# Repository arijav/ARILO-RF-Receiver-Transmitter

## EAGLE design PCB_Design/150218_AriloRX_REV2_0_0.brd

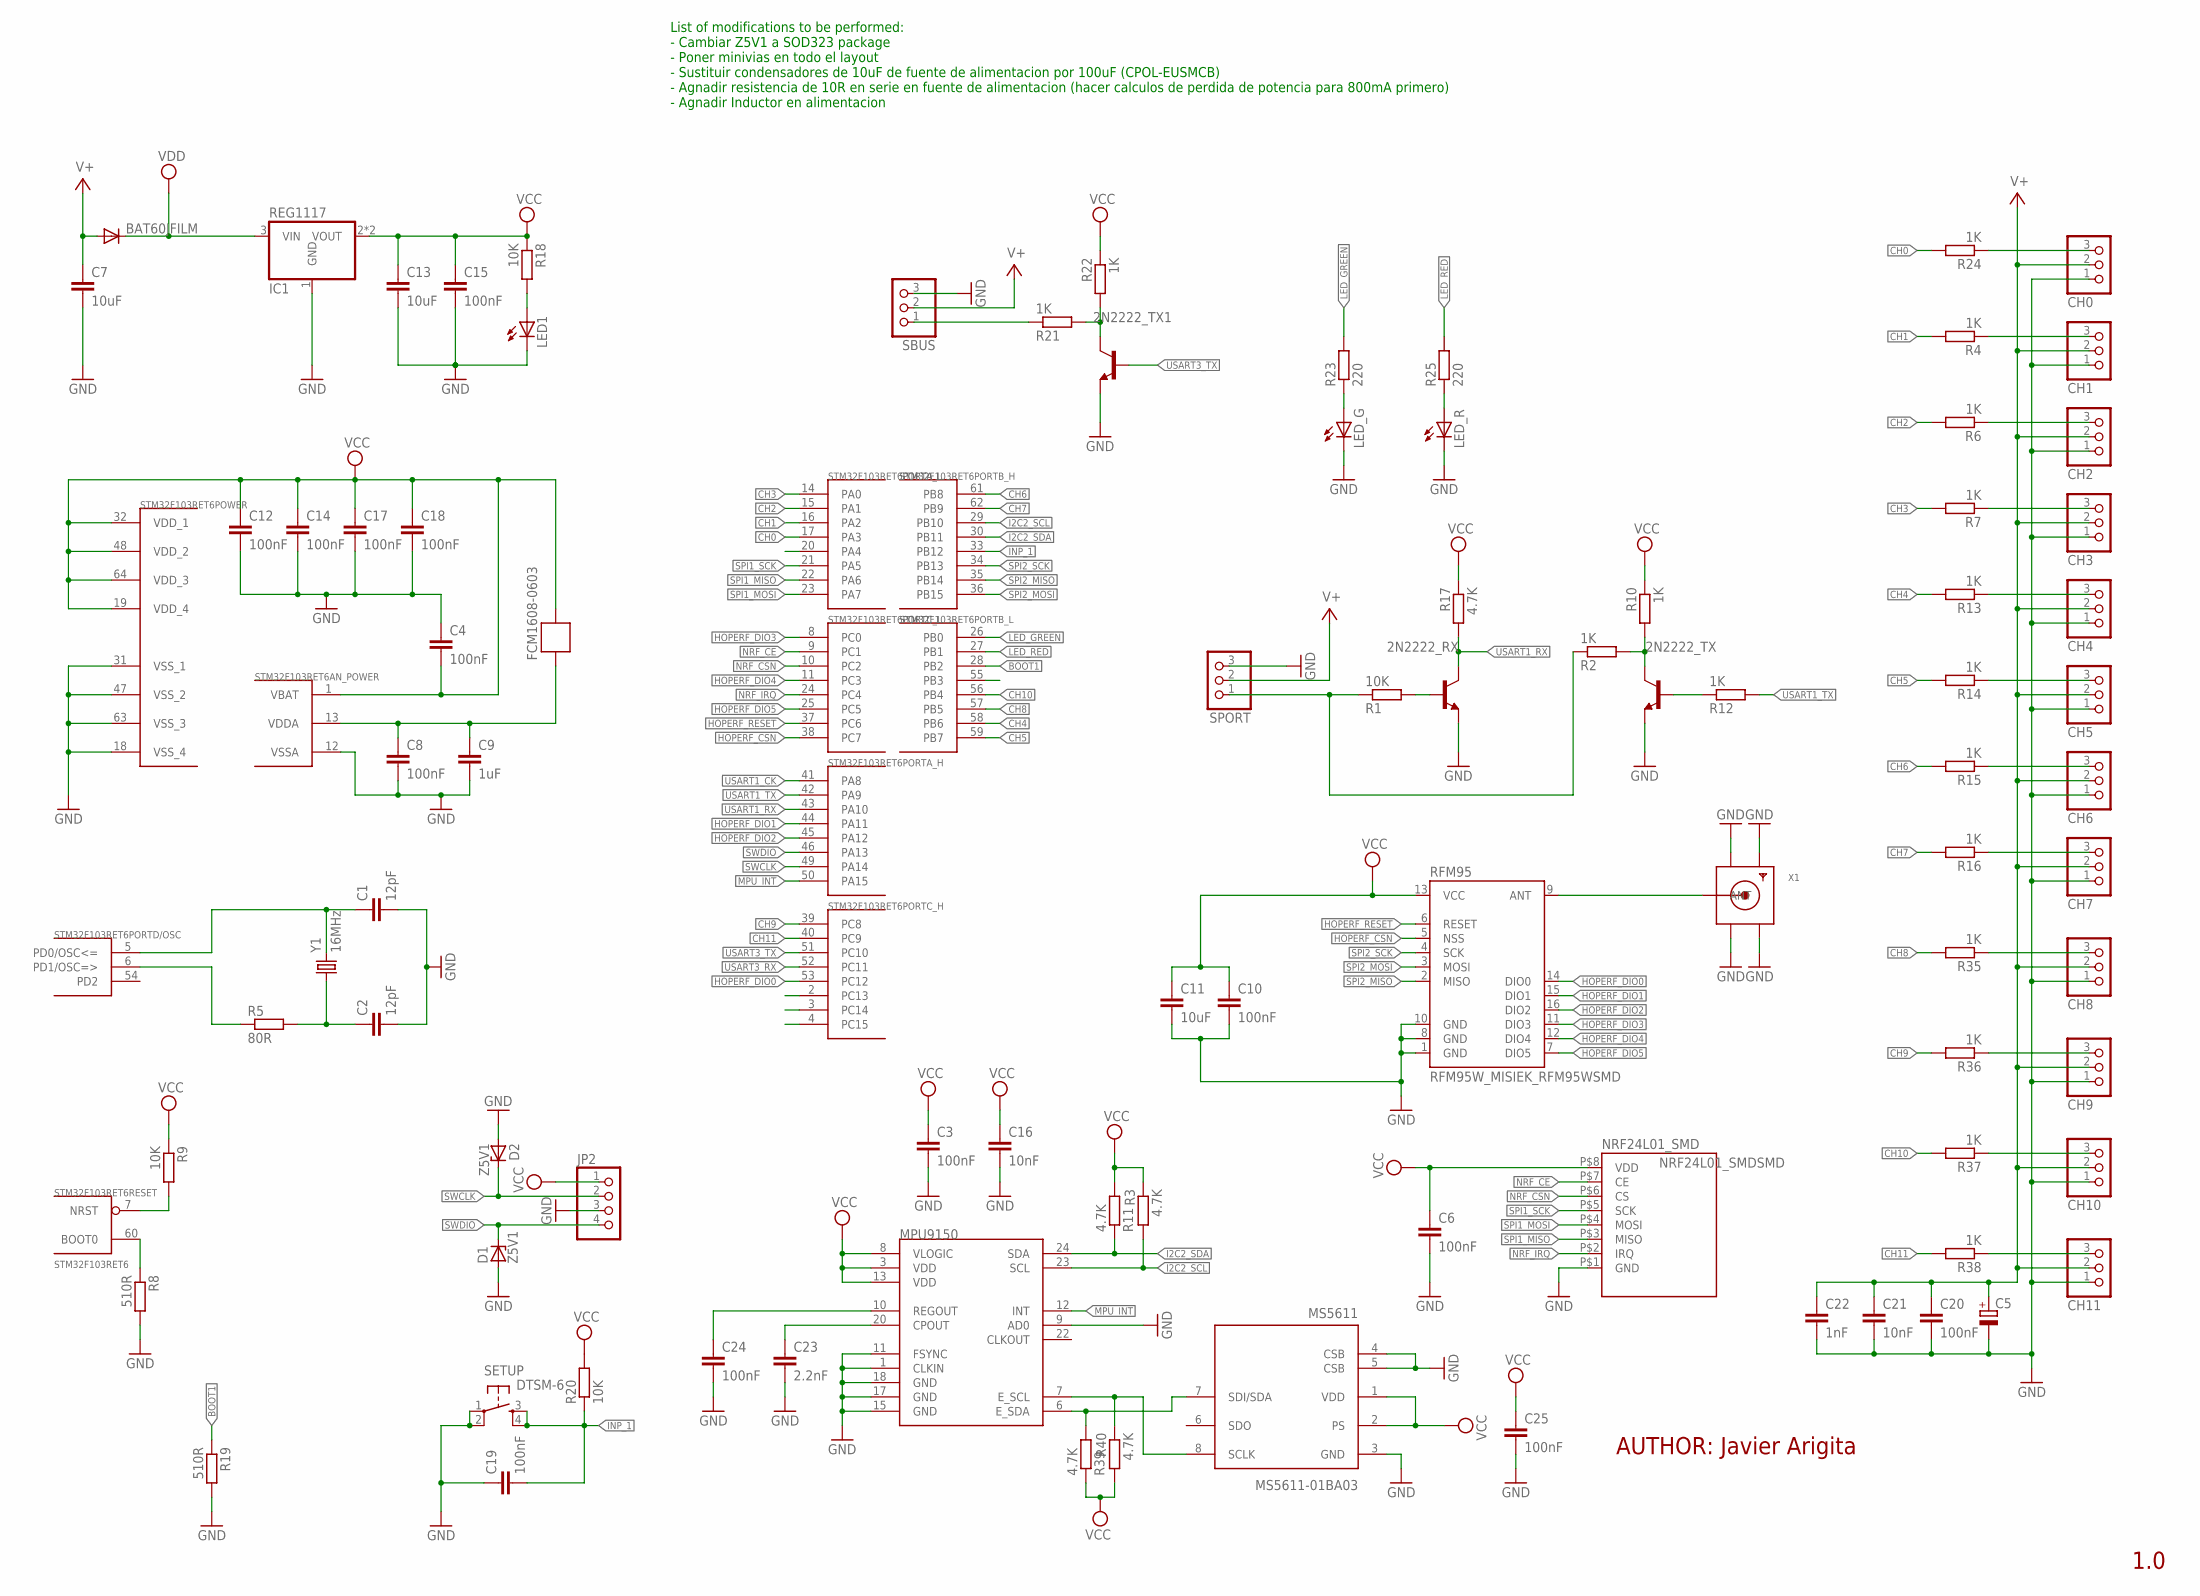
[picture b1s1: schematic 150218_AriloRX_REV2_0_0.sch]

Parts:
2N2222_RX, 2N2222_TX, 2N2222_TX1: MMBT2222ALT1-NPN-SOT23-BEC; SOT23-BEC
BAT60JFILM: DIODE-SOD323-R; SOD323-R
C1, C2: 12pF; RESISTOR_C0603
C3, C4, C6, C8, C10, C12, C14, C15, C17, C18, C19, C20, C24, C25: 100nF; RESISTOR_C0603
C5: CPOL-EUSMCB; SMC_B
C7, C11, C13: 10uF; RESISTOR_C3216
C9: 1uF; RESISTOR_C0603
C16, C21: 10nF; RESISTOR_C0603
C22: 1nF; RESISTOR_C0603
C23: 2.2nF; RESISTOR_C0603
CH0, CH1, CH2, CH3, CH4, CH5, CH6, CH7, CH8, CH9, CH10, CH11: PINHD-1X3; 1X03
D1, D2: Z5V1; SOD80C
FCM1608-0603: FERRITE-BEAD; R0603
IC1: REG1117; SOT223
JP2: PINHD-1X4; 1X04
LED1: LED_LEDCHIP-LED0603; LED_CHIP-LED0603
LED_G: LEDCHIP-LED0603; CHIP-LED0603
LED_R: LEDCHIP-LED0603; CHIP-LED0603
MPU9150: MPU-9150QFN-24-NP; QFN-24-NP
MS5611: MS5611-01BA03; SON125P300X500X100-8N
NRF24L01_SMD: NRF24L01_SMDSMD; NRF24L01_SMD
R1, R9, R18, R20: 10K; RCL_R0603
R2, R4, R6, R7, R10, R12, R13, R14, R15, R16, R21, R22, R24, R35, R36, R37, R38: 1K; RCL_R0603
R3, R11, R17, R39, R40: 4.7K; RCL_R0603
R5: 80R; RCL_R0603
R8, R19: 510R; RCL_R0603
R23, R25: 220; RCL_R0603
RFM95: RFM95W_MISIEK_RFM95WSMD; RFM95W_MISIEK_RFM95W_SMD
SBUS: PINHD-1X3; 1X03
SETUP: DTSM-6
SPORT: PINHD-1X3; 1X03
STM32F103RET6: STM32F103RET6; TQFP64
X1: SMACONNECTOR_EDGE; SMA_EDGELAUNCH
Y1: 16MHz; CRYSTAL-SMD-5X3

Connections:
BOOT1: R19.1, STM32F103RET6.28 (PB2)
CH0: R24.2, STM32F103RET6.17 (PA3)
CH1: R4.2, STM32F103RET6.16 (PA2)
CH2: R6.2, STM32F103RET6.15 (PA1)
CH3: R7.2, STM32F103RET6.14 (PA0)
CH4: R13.2, STM32F103RET6.58 (PB6)
CH5: R14.2, STM32F103RET6.59 (PB7)
CH6: R15.2, STM32F103RET6.61 (PB8)
CH7: R16.2, STM32F103RET6.62 (PB9)
CH8: R35.2, STM32F103RET6.57 (PB5)
CH9: R36.2, STM32F103RET6.39 (PC8)
CH10: R37.2, STM32F103RET6.56 (PB4)
CH11: R38.2, STM32F103RET6.40 (PC9)
GND: 2N2222_RX.E, 2N2222_TX.E, 2N2222_TX1.E, C1.2, C2.2, C3.2, C4.1, C5.-, C6.2, C7.2, C8.2, C9.2, C10.2, C11.2, C12.2, C13.2, C14.2, C15.2, C16.2, C17.2, C18.2, C19.1, C20.2, C21.2, C22.2, C23.2, C24.2, C25.2, CH0.1, CH1.1, CH2.1, CH3.1, CH4.1, CH5.1, CH6.1, CH7.1, CH8.1, CH9.1, CH10.1, CH11.1, D1.A, D2.A, IC1.1 (GND), JP2.3, LED1.C, LED_G.C, LED_R.C, MPU9150.1 (CLKIN), MPU9150.9 (AD0), MPU9150.11 (FSYNC), MPU9150.15 (GND), MPU9150.17 (GND), MPU9150.18 (GND), MS5611.3 (GND), MS5611.4 (CSB), MS5611.5 (CSB), NRF24L01_SMD.P$1 (GND), R8.2, R19.2, RFM95.1 (GND), RFM95.8 (GND), RFM95.10 (GND), SBUS.3, SETUP.1, SETUP.2, SPORT.3, STM32F103RET6.12 (VSSA), STM32F103RET6.18 (VSS_4), STM32F103RET6.31 (VSS_1), STM32F103RET6.47 (VSS_2), STM32F103RET6.63 (VSS_3), X1.GND@1 (GND4), X1.GND@2 (GND3), X1.GND@3 (GND2), X1.GND@4 (GND1)
HOPERF_CSN: RFM95.5 (NSS), STM32F103RET6.38 (PC7)
HOPERF_DIO0: RFM95.14 (DIO0), STM32F103RET6.53 (PC12)
HOPERF_DIO1: RFM95.15 (DIO1), STM32F103RET6.44 (PA11)
HOPERF_DIO2: RFM95.16 (DIO2), STM32F103RET6.45 (PA12)
HOPERF_DIO3: RFM95.11 (DIO3), STM32F103RET6.8 (PC0)
HOPERF_DIO4: RFM95.12 (DIO4), STM32F103RET6.11 (PC3)
HOPERF_DIO5: RFM95.7 (DIO5), STM32F103RET6.25 (PC5)
HOPERF_RESET: RFM95.6 (RESET), STM32F103RET6.37 (PC6)
I2C2_SCL: MPU9150.23 (SCL), R3.2, STM32F103RET6.29 (PB10)
I2C2_SDA: MPU9150.24 (SDA), R11.1, STM32F103RET6.30 (PB11)
INP_1: C19.2, R20.1, SETUP.3, SETUP.4, STM32F103RET6.33 (PB12)
LED_GREEN: R23.2, STM32F103RET6.26 (PB0)
LED_RED: R25.2, STM32F103RET6.27 (PB1)
MPU_INT: MPU9150.12 (INT), STM32F103RET6.50 (PA15)
unnamed: C1.1, STM32F103RET6.5 (PD0/OSC<=), Y1.3 (2)
unnamed: R5.1, STM32F103RET6.6 (PD1/OSC=>)
unnamed: C2.1, R5.2, Y1.1
unnamed: R8.1, STM32F103RET6.60 (BOOT0)
unnamed: 2N2222_TX.C, R2.2, R10.2
unnamed: RFM95.9 (ANT), X1.P (ANT)
unnamed: 2N2222_TX.B, R12.1
unnamed: CH0.3, R24.1
unnamed: LED1.A, R18.2
unnamed: 2N2222_TX1.C, R21.2, R22.2
unnamed: LED_G.A, R23.1
unnamed: CH8.3, R35.1
unnamed: R1.1, R2.1, SPORT.1
unnamed: LED_R.A, R25.1
unnamed: 2N2222_RX.B, R1.2
unnamed: C8.1, C9.1, FCM1608-0603.2, STM32F103RET6.13 (VDDA)
unnamed: CH2.3, R6.1
unnamed: CH4.3, R13.1
unnamed: CH9.3, R36.1
unnamed: CH10.3, R37.1
unnamed: CH11.3, R38.1
unnamed: MPU9150.7 (E_SCL), MS5611.8 (SCLK), R40.1
unnamed: MPU9150.6 (E_SDA), MS5611.7 (SDI/SDA), R39.2
unnamed: CH3.3, R7.1
unnamed: CH6.3, R15.1
unnamed: C23.1, MPU9150.20 (CPOUT)
unnamed: CH5.3, R14.1
unnamed: CH7.3, R16.1
unnamed: C24.1, MPU9150.10 (REGOUT)
unnamed: CH1.3, R4.1
NRF_CE: NRF24L01_SMD.P$7 (CE), STM32F103RET6.9 (PC1)
NRF_CSN: NRF24L01_SMD.P$6 (CS), STM32F103RET6.10 (PC2)
NRF_IRQ: NRF24L01_SMD.P$2 (IRQ), STM32F103RET6.24 (PC4)
NSRST: R9.2, STM32F103RET6.7 (NRST)
SBUS: R21.1, SBUS.1
SPI1_MISO: NRF24L01_SMD.P$3 (MISO), STM32F103RET6.22 (PA6)
SPI1_MOSI: NRF24L01_SMD.P$4 (MOSI), STM32F103RET6.23 (PA7)
SPI1_SCK: NRF24L01_SMD.P$5 (SCK), STM32F103RET6.21 (PA5)
SPI2_MISO: RFM95.2 (MISO), STM32F103RET6.35 (PB14)
SPI2_MOSI: RFM95.3 (MOSI), STM32F103RET6.36 (PB15)
SPI2_SCK: RFM95.4 (SCK), STM32F103RET6.34 (PB13)
SWCLK: D2.C, JP2.2, STM32F103RET6.49 (PA14)
SWDIO: D1.C, JP2.4, STM32F103RET6.46 (PA13)
USART1_CK: STM32F103RET6.41 (PA8)
USART1_RX: 2N2222_RX.C, R17.2, STM32F103RET6.43 (PA10)
USART1_TX: R12.2, STM32F103RET6.42 (PA9)
USART3_RX: STM32F103RET6.52 (PC11)
USART3_TX: 2N2222_TX1.B, STM32F103RET6.51 (PC10)
V+: BAT60JFILM.A, C5.+, C7.1, C20.1, C21.1, C22.1, CH0.2, CH1.2, CH2.2, CH3.2, CH4.2, CH5.2, CH6.2, CH7.2, CH8.2, CH9.2, CH10.2, CH11.2, SBUS.2, SPORT.2
VCC: C3.1, C4.2, C6.1, C10.1, C11.1, C12.1, C13.1, C14.1, C15.1, C16.1, C17.1, C18.1, C25.1, FCM1608-0603.1, IC1.2 (VOUT), IC1.4 (VOUT), JP2.1, MPU9150.3 (VDD), MPU9150.8 (VLOGIC), MPU9150.13 (VDD), MS5611.1 (VDD), MS5611.2 (PS), NRF24L01_SMD.P$8 (VDD), R3.1, R9.1, R10.1, R11.2, R17.1, R18.1, R20.2, R22.1, R39.1, R40.2, RFM95.13 (VCC), STM32F103RET6.1 (VBAT), STM32F103RET6.19 (VDD_4), STM32F103RET6.32 (VDD_1), STM32F103RET6.48 (VDD_2), STM32F103RET6.64 (VDD_3)
VDD: BAT60JFILM.C, IC1.3 (VIN)

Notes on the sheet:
AUTHOR: Javier Arigita
1.0
List of modifications to be performed: - Cambiar Z5V1 a SOD323 package - Poner minivias en todo el layout - Sustituir condensadores de 10uF de fuente de alimentacion por 100uF (CPOL-EUSMCB) - Agnadir resistencia de 10R en serie en fuente de alimentacion (hacer calculos de perdida de potencia para 8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

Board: 2 copper layers, 90 parts (13 on the bottom side), 77 nets, no tracks yet.

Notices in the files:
parts and their libraries:
SparkFun-Sensors: Licensing: CC v3.0 Share-Alike You are welcome to use this library for commercial purposes.
